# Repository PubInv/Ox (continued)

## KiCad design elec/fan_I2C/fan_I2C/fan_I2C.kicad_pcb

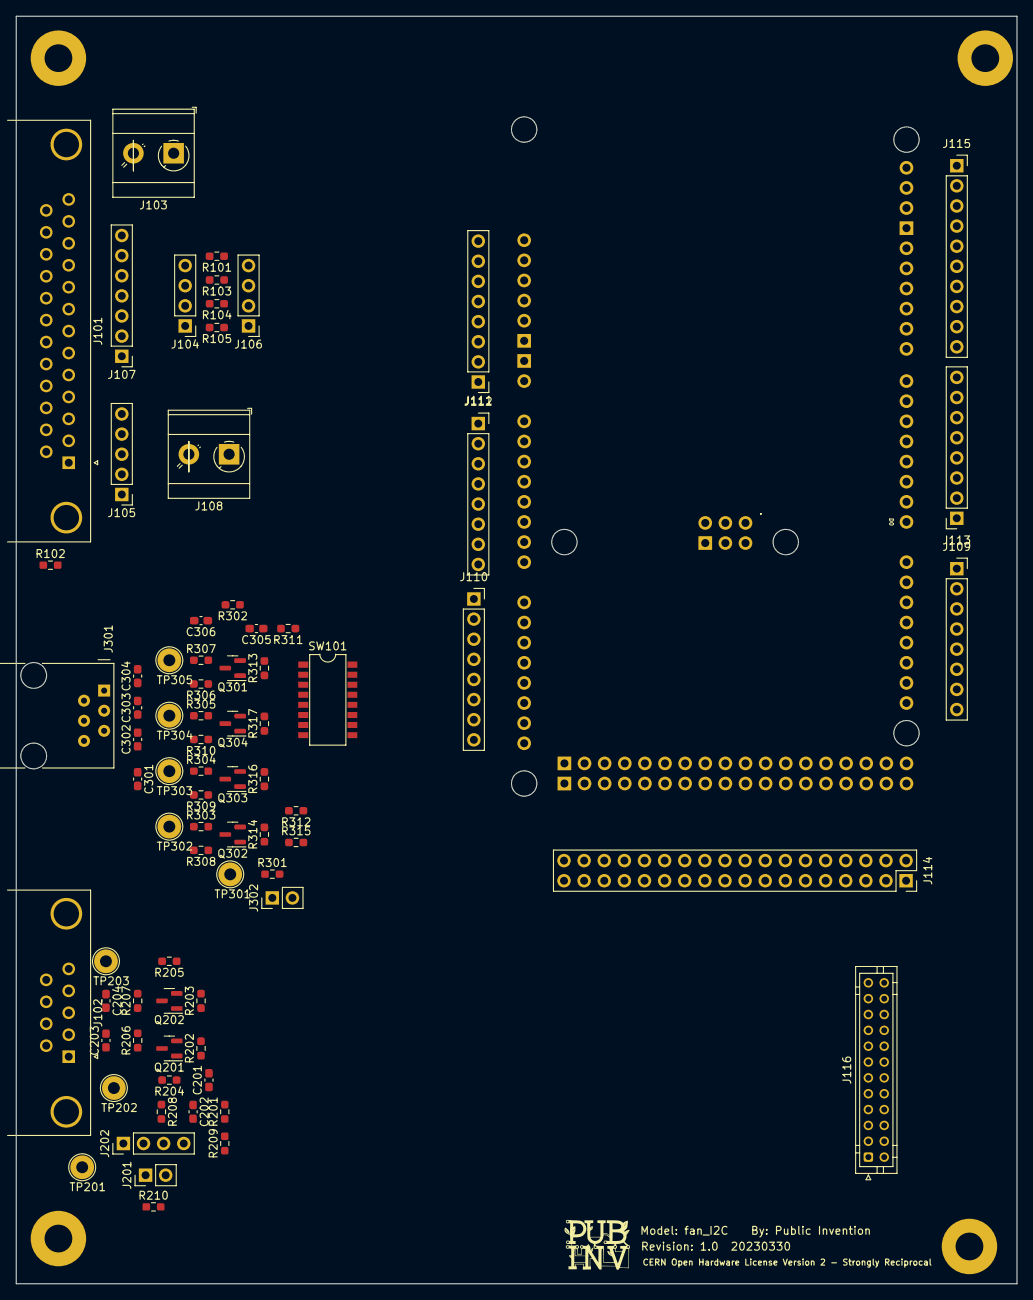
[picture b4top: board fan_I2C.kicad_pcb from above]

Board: 2 copper layers, 126.3 x 160.0 mm, 78 parts (0 on the bottom side), 123 nets, no tracks yet.

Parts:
C201, C202, C305, C306: 1uF; C_0603_1608Metric_Pad1.08x0.95mm_HandSolder
C203, C204, C301, C302, C303, C304: 39PF; C_0603_1608Metric_Pad1.08x0.95mm_HandSolder
J101: DB25_Female_MountingHoles; DSUB-25_Female_Horizontal_P2.77x2.84mm_EdgePinOffset4.94mm_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
J102: DB9_Female_MountingHoles; DSUB-9_Female_Horizontal_P2.77x2.84mm_EdgePinOffset4.94mm_H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
J103, J108: Screw_Terminal_01x02; TerminalBlock_MetzConnect_Type073_RT02602HBLU_1x02_P5.08mm_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
J104, J106, J202: Conn_01x04; PinHeader_1x04_P2.54mm_Vertical
J105: Conn_01x05; PinHeader_1x05_P2.54mm_Vertical
J107: Conn_01x07; PinHeader_1x07_P2.54mm_Vertical
J109, J110, J112, J113: Conn_01x08; PinSocket_1x08_P2.54mm_Vertical
J111: Conn_01x08; PinHeader_1x08_P2.54mm_Vertical
J114: Conn_02x18_Odd_Even; PinSocket_2x18_P2.54mm_Vertical
J115: Conn_01x10_MountingPin; PinSocket_1x10_P2.54mm_Vertical
J116: Conn_02x12_Odd_Even; JST_PHD_B24B-PHDSS_2x12_P2.00mm_Vertical
J201, J302: 0.100_2Pin; PinHeader_1x02_P2.54mm_Vertical
J301: RJ12_6P6C_HORZ; RJ12_Amphenol_54601
Q201, Q202, Q301, Q302, Q303, Q304: BSS138; SOT-23
R101, R103, R104, R105: 540R; R_0603_1608Metric_Pad0.98x0.95mm_HandSolder
R102, R209, R210, R303, R304, R305, R307, R312, R315: DNI; R_0603_1608Metric_Pad0.98x0.95mm_HandSolder
R201, R208, R301, R302, R311: 1R; R_0603_1608Metric_Pad0.98x0.95mm_HandSolder
R202, R203, R204, R205, R308, R313, R316, R317: 10K; R_0603_1608Metric_Pad0.98x0.95mm_HandSolder
R206, R207: 39R; R_0603_1608Metric_Pad0.98x0.95mm_HandSolder
R306, R309, R310, R314: 1K; R_0603_1608Metric_Pad0.98x0.95mm_HandSolder
SW101: SW_DIP_x08; SMDIP-16_L11.39_W6.7mm
TP201: I2C_VCC; TestPoint_Loop_D2.54mm_Drill1.5mm_Beaded
TP202: SCL_5V; TestPoint_Loop_D2.54mm_Drill1.5mm_Beaded
TP203: SDA_5V; TestPoint_Loop_D2.54mm_Drill1.5mm_Beaded
TP301: ControllerVCC; TestPoint_Loop_D2.54mm_Drill1.5mm_Beaded
TP302: CPIO; TestPoint_Loop_D2.54mm_Drill1.5mm_Beaded
TP303: SCK; TestPoint_Loop_D2.54mm_Drill1.5mm_Beaded
TP304: COPI; TestPoint_Loop_D2.54mm_Drill1.5mm_Beaded
TP305: nCS; TestPoint_Loop_D2.54mm_Drill1.5mm_Beaded
XA101: Arduino_Due_Shield

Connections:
5V3: J114.1, XA101.5V3 (5V)
5V4: J114.2, XA101.5V4 (5V)
+3.3V: J106.2, J111.5, R101.1, R103.1, R104.1, R105.1, R311.1, XA101.3V3 (3.3V)
+5V: J111.4, R302.1, XA101.5V1 (5V)
+12V: J302.2, R301.2
/I2C_LevelShift/+3V3Local: C201.1, Q201.1 (G), Q202.1 (G), R201.2, R202.1, R203.1
/I2C_LevelShift/+5LevelShift: R208.2, R209.2
/I2C_LevelShift/+5VLocal: C202.1, R204.1, R205.1, R208.1
/I2C_LevelShift/+12forSPIPeripherial: J201.2, R210.2
/I2C_LevelShift/I2C_VCC: J201.1, J202.1, R209.1, R210.1, TP201.1
/I2C_LevelShift/SCL_5V: C203.1, J102.2, J202.2, R206.1, TP202.1
/I2C_LevelShift/SDA_5V: C204.1, J102.4, J202.4, R207.1, TP203.1
/SPI_ControllerLevel_Shifter/+3V3Local: C305.1, Q301.1 (G), Q302.1 (G), Q303.1 (G), Q304.1 (G), R311.2, R313.1, R314.1, R316.1, R317.1
/SPI_ControllerLevel_Shifter/+5VLocal: C306.1, R302.2, R306.1, R308.1, R309.1, R310.1
/SPI_ControllerLevel_Shifter/CIPO: C301.1, J301.6, Q302.3 (D), R303.1, R308.2, TP302.1
/SPI_ControllerLevel_Shifter/COPI: C303.1, J301.2, Q304.3 (D), R305.1, R310.2, TP304.1
/SPI_ControllerLevel_Shifter/COPI_nCS: Q301.2 (S), R307.2, R313.2, SW101.1, SW101.2, SW101.3, SW101.4, SW101.5, SW101.6, SW101.7, SW101.8
/SPI_ControllerLevel_Shifter/C_SCK: C302.1, J301.4, Q303.3 (D), R304.1, R309.2, TP303.1
/SPI_ControllerLevel_Shifter/ControllerVcc: J301.5, J302.1, R301.1, TP301.1
/SPI_ControllerLevel_Shifter/nCS: C304.1, J301.1, Q301.3 (D), R306.2, R307.1, TP305.1
AREF: J115.3, XA101.AREF
CANR: J110.7, XA101.CANR (CANRX)
CANT: J110.8, XA101.CANT (CANTX)
CIPO: Q302.2 (S), R303.2, R312.2, R314.2, XA101.MISO (SPI_MISO)
COPI: Q304.2 (S), R305.2, R317.2, XA101.MOSI (SPI_MOSI)
D0: J113.1, XA101.D0 (D0/RX0)
D1: J113.2, XA101.D1 (D1/TX0)
D23: J109.7, J114.4, XA101.D23
D25: J114.6, XA101.D25
D27: J114.8, XA101.D27
D29: J114.10, XA101.D29
D31: J114.12, XA101.D31
D33: J114.14, XA101.D33
D35: J114.16, XA101.D35
D37: J114.18, XA101.D37
D39: J114.20, XA101.D39
D41: J114.22, XA101.D41
D43: J114.24, XA101.D43
D45: J114.26, XA101.D45
D47: J114.28, XA101.D47
D49: J114.30, XA101.D49
D51: J114.32, XA101.D51
DAC0: J110.5, XA101.DAC0
DAC1: J110.6, XA101.DAC1
GND: C201.2, C202.2, C203.2, C204.2, C301.2, C302.2, C303.2, C304.2, C305.2, C306.2, J101.0 (PAD), J102.0 (PAD), J102.3, J102.6, J102.7, J102.8, J102.9, J106.1, J108.1, J111.2, J111.3, J114.35, J114.36, J115.4, J202.3, J301.3, R102.2, R315.1, XA101.GND1 (GND), XA101.GND2 (GND), XA101.GND3 (GND), XA101.GND5 (GND), XA101.GND6 (GND)
unnamed: J101.1, J105.1
unnamed: J101.2, J105.2
unnamed: J101.3, J105.3
unnamed: J101.4, J105.4
unnamed: J101.5, J104.1, R105.2
unnamed: J101.6, J104.2, R104.2
unnamed: J101.7, J104.3, R103.2
unnamed: J101.8, J104.4, R101.2
unnamed: J101.9, J101.10, J101.11, J101.12, J103.2
unnamed: J101.13, J106.4
unnamed: J101.14, J101.15, J101.16, J101.17, J103.1, R102.1
unnamed: J101.18, J107.1
unnamed: J101.19, J107.2
unnamed: J101.20, J107.3
unnamed: J101.21, J107.4
unnamed: J101.22, J107.5
unnamed: J101.23, J107.6
unnamed: J101.24, J107.7
unnamed: J101.25, J106.3
unnamed: J105.5, J108.2
unnamed: J109.1, XA101.D14 (D14/TX3)
unnamed: J109.2, XA101.D15 (D15/RX3)
unnamed: J109.3, XA101.D16 (D16/TX2)
unnamed: J109.4, XA101.D17 (D17/RX2)
unnamed: J109.5, XA101.D18 (D18/TX1)
unnamed: J109.6, XA101.D19 (D19/RX1)
unnamed: J110.1, XA101.A8
unnamed: J110.2, XA101.A9
unnamed: J110.3, XA101.A10
unnamed: J110.4, XA101.A11
unnamed: J111.1, XA101.VIN
unnamed: J111.6, XA101.RST1 (RESET)
unnamed: J111.7, XA101.IORF (IOREF)
unnamed: J112.1, XA101.A0
unnamed: J112.2, XA101.A1
unnamed: J112.3, XA101.A2
unnamed: J112.4, XA101.A3
unnamed: J112.5, XA101.A4
unnamed: J112.6, XA101.A5
unnamed: J112.7, XA101.A6
unnamed: J112.8, XA101.A7
unnamed: J113.3, XA101.D2
unnamed: J113.4, XA101.D3
unnamed: J113.5, XA101.D4 (D4_CS1)
unnamed: J113.6, XA101.D5
unnamed: J113.7, XA101.D6
unnamed: J113.8, XA101.D7
unnamed: J114.3, XA101.D22
unnamed: J114.5, XA101.D24
unnamed: J114.7, XA101.D26
unnamed: J114.9, XA101.D28
unnamed: J114.11, XA101.D30
unnamed: J114.13, XA101.D32
unnamed: J114.15, XA101.D34
unnamed: J114.17, XA101.D36
unnamed: J114.19, XA101.D38
unnamed: J114.21, XA101.D40
unnamed: J114.23, XA101.D42
unnamed: J114.25, XA101.D44
unnamed: J114.27, XA101.D46
unnamed: J114.29, XA101.D48
unnamed: J114.31, XA101.D50
unnamed: J114.33, XA101.D52 (D52_CS2)
unnamed: J114.34, XA101.D53
unnamed: J115.5, XA101.D13
unnamed: J115.6, XA101.D12
unnamed: J115.7, XA101.D11
unnamed: J115.8, XA101.D10 (D10_CS0)
unnamed: J115.9, XA101.D9
unnamed: J115.10, XA101.D8
unnamed: Q201.3 (D), R204.2, R206.2
unnamed: Q202.3 (D), R205.2, R207.2
unnamed: R312.1, R315.2
SCL: Q201.2 (S), R202.2, XA101.D21 (D21/SCL)
SCL1: J115.1, XA101.SCL1
SDA: Q202.2 (S), R203.2, XA101.D20 (D20/SDA)
SDA1: J115.2, XA101.SDA1
SPI_SCK: Q303.2 (S), R304.2, R316.2, XA101.SCK (SPI_SCK)

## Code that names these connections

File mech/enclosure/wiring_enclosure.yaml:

#templates for generalized connectors
#utilizes https://github.com/wireviz/WireViz
templates:
  - &template_con
    type: Anderson Power SB50 SB
    subtype:  Dual
    pinlabels: [V+, V-, V+, V-]
  - &template_wire
    gauge: 6.00 mm2
    length: 0.2
    colors: [RD,BK,RD,BK]
    category: bundle
  - &ac_hookup
        wirecount: 3
        length: 0.2 //15ft
        category: bundle
        colors: [BK,WH,GN]
        gauge: 12 awg
  - &tc_hookup
        wirecount: 2
        length: 0.02
        category: bundle
        colrs: [YL,RD]
cables:   # dictionary of all used cables and wires
  W0:
    gauge: 1 mm2
    show_equiv: true
    length: 0.5
    color_code: IEC
    wirecount: 3
    category: bundle

  W1:    # unique cable designator/name
    gauge: 6.0 mm2
    # defaults to false; can auto-convert between mm2 and AWG and display the result when set to true
    show_equiv: true
     # <int/float> is assumed to be in meters unless <unit> is specified
                                # e.g. length: 2.5 -> assumed to be 2.5 m
                                # or   length: 2.5 ft -> "ft" is used as the unit
                                # Units are not converted during BOM generation;
                                # different units result in separate BOM entries.
    length: 0.5
    #color_code: IEC
    wirecount: 2
    category: bundle
    colors: [RD,BK]     # list of colors (see below)
    wirelabels: [V+,V-] # optional; one label for each wire
  W2:
    gauge: 0.25 mm2
    show_equiv: true
    length: 0.5
    color_code: IEC
    wirecount: 24
    category: bundle

  W3: #TC 1
    <<: *tc_hookup
    length: 0.2
    show_equiv: true
  W4: #TC 2
    <<: *tc_hookup
    length: 0.2
    show_equiv: true
  W5: #TC 3
    <<: *tc_hookup
    length: 0.2
    show_equiv: true
  W6: 
    <<: *template_wire

  W7: #DC powersupply_12v
    <<: *ac_hookup

  W8: #DC powersupply_24v
    <<: *ac_hookup

  W9: #DC powersupply_programmable
    <<: *ac_hookup

  power_cord:
      wirecount: 3
      length: 5000 //15ft
      category: bundle
      colors: [BK,WH,GN]

connectors:  # dictionary of all used connectors
  ferrule_spade:  # unique connector designator/name
    style: simple
    autogenerate: true
    type: Spade ferrule
    subtype: spade
  ferrule_crimp:
    style: simple
    autogenerate: true
    type: Crimp ferrule
    subtype: 0.25 mm²
    color: YE

  CN2:
    type: JST PHDR-24VS
    subtype: female
    pincount: 24
    pinlabels: [VS+, VO+, VS-, VO-, POK, GND, PAR, VSET, EN-, GND, EN+, AUX, ACI, GND, VCI, GND, AUX, GND, SCL, SDA, AUX, GND, RX, TX]

  X1:
    type: D-Sub
    subtype: male
    pincount: 9
#    pinlabels: []

  X2:
    type: D-Sub
    subtype: male
    pincount: 25
    pinlabels: [NP,NP,NP,NP,PWM1,PWM2,PWM3,PWM4,+12v,+12v,+12v,+12v,NP,GND,GND,GND,GND,PWM5,PWM6,PWM7,PWM8,PWM9,PWM10,PWM11,NP]
    notes: Pin 5-8 have 470 Ohm Pull Up resistors
  X3:
    <<: *template_con
  X4:
    <<: *template_con
  X5:
    <<: *template_con
  X6:
    <<: *template_con
  Arduino_Due:
    type: jumpers
    pinlabels: [TX,RX, TX1, RX1, SDA, SCL, VIN, GND, A0, A1, A2, A3, A4, A5, A6, A7, A8, A9, A10, A11, D0, D1, D2, D3, D4, D5, D6, D7, D8, D9, D10, D11, D12, D13, D14, D15, D16, D17, D18, D19, D20, D21, 3.3V, GND]
  Fan_Interface:
    type: jumpers
    pinlabels: [ nFAN1_PWM, FAN1_FG, nFAN2_PWM, FAN2_FG, FAN3_FG, nFAN3_PWM, FAN4_FG, nFAN4_PWM]

connections:  # list of all connections to be made between cables and connectors
  -
    - ferrule_crimp
    - W1: [1-2]
    - ferrule_crimp
  -
    - CN2: [1-24]
    - W2: [1-24]
    - ferrule_crimp
  -
    - X1: [5,2,3]
    - W0: [1-3]
    - Arduino_Due: [D0,D1,D21]
  -
    - X3: [1-4]
    - W3: [1-4]
    - ferrule_crimp
  -
    - X4: [1-4]
    - W4: [1-4]
    - ferrule_crimp
  -
    - X5: [1-4]
    - W5: [1-4]
    - ferrule_crimp
  -
     - ferrule_crimp
     - W7: [1-3]
  -  
     - ferrule_crimp
     - Arduino_Due: [A0, D4, D9, D18, D19, D51, 3.3V, GND]
     - nFAN1_PWM
     - FAN1_FG
     - nFAN2_PWM
     - FAN2_FG
     - FAN3_FG
     - nFAN3_PWM
     - FAN4_FG
     - nFAN4_PWM
     
#  -

#additional_bom_items:  # custom items to add to BOM
#  - zip ties           # BOM item (see below)

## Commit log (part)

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2023-08-17 Add U1 rack mount on right.
2023-08-17 Add a multitransform but it overwrites other features and DB9 has dependancy cycle and not recompute.
2023-08-17 Update README.md
    Add the OEDCS1-Aug-17.JPG image to the README.md at mech/enclosure/AssemblyPhotos
2023-08-17 imported Lee's changed inputs into the folder Control Board,
    Also added in Robert's pin labels
    ToDo: clean up broken links, and import in the layout files from Lee's project
    Clean up the fan control pinout, the DB25 is a bit of a mess
    consider using IDC to DB25 connectors for ease of assembly and installation.
2023-08-18 Add Lees PublicInvention submodule library. Update Control V1 project and schematic for new library.
2023-08-19 Rename Due CFC Pinouts to Due CFC Pinouts.md
2023-08-19 Update README.md
    Add wiring of thermocouple amplifiers of Unit 1.
2023-08-21 Update README.md
    Update fan supply voltage and indicated switched.
2023-08-21 Switch to FAN POWER.
2023-08-21 Update README.md
    Fix, swap, function on DB25 pins 3 and 7
2023-08-21 Add net names to fan controler block.
2023-08-22 Update README.md
    Add links for On line schematic viewing from **Kicanvas** of the current schematics.
2023-08-22 Add fan circuits. Add thermocouple interface circuits.
2023-08-23 fixing a bug in the data logging, seems to be working now
2023-08-23 Add footrpint to Max31850 module.
2023-08-24 debugged getting the fan test working again
2023-08-24 Add footprints for thermoucouple modules to schematic and PCB. This commit does NOT capture the library changes.
2023-08-24 Flip the front panel around.
2023-08-24 fan is now working properly
2023-08-24 Update schematic for MCP9600 I2C thermocouple.
2023-08-25 Next and place thermocouple boards.
2023-08-25 Fix swome ERC errors.
2023-08-25 Add header sockets. Refine PCB placement, temprature sensors.
2023-08-26 Update README.md
    Begin Due Pin Wiring Table
2023-08-27 very significant rewrite and simplication of the main algorithms
2023-08-27 Update README.md
    Add more details to Due wiring table. Up to D19.
2023-08-27 Net name congruancy to D35. Add named test points.
2023-08-27 Update README.md
    Finish the Due pin table.
2023-08-27 Update README.md
    Update of Due Pin Number table resolving some "???" and more.
2023-08-28 Update README.md
    Update to Due pin wiring after team review.
2023-08-28 Changes during team review.
2023-08-28 Lots of routing. Lots remaining.
2023-08-28 Finishe routing on enlarged perimeter.
2023-08-28 fixing bug #148 by inceasing MAX_TASKS and some other improvements
2023-08-28 using sentinel numbers in report
2023-08-29 Fixing bug #175
2023-08-30 Update parts in schematic for BOM generation.
2023-08-30 Add BOM spread sheet and a JLCPCB BOM.
2023-08-30 Update README.md
    Update the Control v1 README.md with KICanvas link to the PCB
2023-08-30 Add footprints to KiCad board. Make simple Due and Ethernte boards for pullin into FreeCAD assembly and do so.
2023-08-30 Preparation for the stage2 heater code
2023-08-30 changing obsolete file name
2023-08-30 further refactoring of state machine
2023-08-31 significant refactoring to make Stage2 heater
2023-08-31 stage2 report working now
2023-08-31 Update README.md
    Make more descriptive of the scope of the content.
2023-08-31 Add folder and a README.md for capture of Serial number 2 fabrication.
2023-08-31 Update README.md
    Add more information about serial number 2 build.
2023-08-31 some progress on Stage2 desgin
2023-09-01 debugging of stage2 related code
2023-09-02 working mostly on improving ability to survive resets and other debugging
2023-09-03 some more refacotrings (no build attempted yet
2023-09-03 now the heater code compiles
2023-09-04 checking if isinf on ohms values to avoid string being printed and messing up Cumulocity
2023-09-04 Update README.md
    Add the acronym OEDCS with the explanation.
2023-09-04 removing intermediate directories that we used for passing code but are now breaking the build on Windows machines (or maytbe all)
2023-09-05 Remove submodult to Watchdog example code.
2023-09-05 in middle of debuggin, stacks[0] point on COG_HAL appears to be incorrect by the time it used
2023-09-05 Update Stage2_Heater.md
    added ethernet shield pin references for SPI
2023-09-06 Add imaes of Controller V1 PCB and Assys from JLCPCB.
2023-09-06 Add a Controller support bracket.
2023-09-06 Update README.md
    With PWA
2023-09-06 fixed majore bug that was preventing the addition of the ramp up time
2023-09-06 Image Making print out more accurate.
2023-09-06 Create README.md
    Describe the files.
2023-09-07 turning off debugging statments
2023-09-07 Update Watchdog to rev 6. Save to flash only when D12 low. Increment flash count on reset. Add serial number to structure.
2023-09-08 Change PCB gap on ControllerSupport from 1mm to 2mm.
2023-09-09 Update README.md
    Spaces to format better.
2023-09-11 Create networking
2023-09-12 Changing from D4 to D5 for temperature reads
2023-09-12 Incrementing version for change in thermocouple pin.
2023-09-13 added stage2 hal changes
2023-09-13 adding target fore due_stage2_heater
2023-09-13 intermediate files, not compiling
2023-09-13 compiling, but untested
2023-09-13 committing some debugging statements
2023-09-13 Update Stage2_Heater.md
    updated pinout docs
2023-09-14 OnePinHeater refactoring, changes to makefile
2023-09-14 major refactoring of network code to remove it from tha task and put it in the hal
2023-09-14 Adding two files
2023-09-14 creatign Stage2 Network class
2023-09-14 refactoring file names
2023-09-14 Add files via upload
    Full resolution Serial number 2 photographs.
2023-09-15 fix networking code
2023-09-15 fix W5x00 init error message
2023-09-15 adding immature test program that does not seem to have any bad readings even with fan on
2023-09-15 revving version number
2023-09-16 beginning of the 5-knob work
2023-09-16 Update README.md
    Add more MAC addresses
2023-09-16 initial checkin, reading commands but commands do nothing, this branch is broken for now
2023-09-16 Some bugs from 263 fixed, but Network may not be working.
2023-09-16 some improvements
2023-09-17 intermediate waypoint
2023-09-17 Update state_machine_manager.cpp
    enabled ramp down target temp, otherwise computeRampDnTargetTemp returns float t unmodified
2023-09-17 signifianct work, and some realizations for simplifications
2023-09-18 fix memory leaks inside parsing state params and phases
2023-09-18 adding DueFlashStorage library
2023-09-18 adding wattage limitation
2023-09-18 Update README.md
    Link to an issue for how to find an ODECS IP address.
2023-09-18 Create README.md
    Description of Files / Folders
2023-09-18 latest
2023-09-19 removing param script retrieval
2023-09-19 providing a back door for testing when you don't have 3 thermocouples as a compile time switch
2023-09-19 change generation of max address to set last bit 0 for cfc and 1 for stage2
2023-09-19 revert my last change
2023-09-20 minor udp fix
2023-09-20 intermediate code, unknown state
2023-09-20 Update README.md
    Add MAC for OEDCS Serial number 2.
2023-09-20 moving back to 3.11.0 for Dallas OneWire
2023-09-20 reveting to use standard thermocooples for Stage2
2023-09-21 removing stray debugging statements
2023-09-21 fixing but with temperature jump
2023-09-22 fixing global start temperature bug
2023-09-22 Fixing an incorrect variable, passing GLOBAL_RECENT_TEMP when it should have been WARM_UP_BEGIN_TIME, cause ramp up to be too high
2023-09-22 update to debugging
2023-09-22 Add Due mechanical files. Add step for the Due Ethernet Control v1 assembly.
2023-09-22 compatability with SPI thermocouple boards and to ensure there is always an initial good read before compair
2023-09-23 Update Fan 4-wire cable interface
2023-09-26 Improving Make Target
2023-09-27 now compiles Stage2Heater code successfully
2023-09-27 changing precision of printed value
2023-09-27 Add simulation file and result as PNG.
2023-09-27 Update README.md
    Add a README.md to explain the simulation and simulation files.
2023-09-27 Update platformio.ini
    added support for rPi needs to have arm compiler defined
    per
    https://github.com/platformio/platform-ststm32/issues/404#issuecomment-673693211
2023-09-27 Update README.md
    Correct some novel spelling.
    Improve formatting of notes.
    Add description of limitation of the simulation.
2023-09-28 Add a simulation workbook to RCRC simulation.
2023-09-28 Update README.md
    Update with link to this schematic.
2023-09-28 changing PID Tunings
2023-10-02 Update polarity of connections to the GPOLY to correct the signs of the terms in the output.
2023-10-04 improve casting in TC toleration time math and fixing major bug in the use of the PID controller.
2023-10-05 adding debugging to the test program by using a fork with more
2023-10-06 Create README.md
    Add markdown with previews of photos.
2023-10-06 Update README.md
    Add link to folder of OEDCS Serial number 1 device photos.
2023-10-07 Update for JLCPCB part number of J10
2023-10-10 Copy PCB version 1.0 to version 1v1 and delete stale files. No other changes.
2023-10-10 Fix J10 backwards.
2023-10-11 Place many of new components. Still need to place SSR parts.
2023-10-11 Update README.md
    Update most of the PCB information. THIS PCB is not yet finished.
2023-10-11 Added schematic components for display header
2023-10-11 cosmetic schematic layouc changes
2023-10-11 Add power supply enable circuits. Add shutdown button.
2023-10-12 Make first cut JLCPCB BOM.
2023-10-12 unified 1R and 1R0 references
2023-10-12 Update README.md
    Add display_interface.kicad_sch to the README.MD
2023-10-12 Create Safety and Hazards Failure Effects Mode Analysis
2023-10-13 Some component placement for display and I2C.
2023-10-13 Still working on a few JLCPCB part numbers for components, headers - sockets.
2023-10-13 Fill ground.
2023-10-13 Getting close to order of PWAs for Control 1v1.
2023-10-13 Add the files JLCPCB modified for their order process.
2023-10-13 Add Breadboard30P.
2023-10-16 Add the Manufacturing files and notes as used for the JLCPCB order on 20231016,
2023-10-17 Holes in flanges but they disappear.
2023-10-17 Changes to change headders to sockets. Scockets for thermcouple amplifiers.
2023-10-17 updated manufacturing bom and positino files
2023-10-18 A 3D file for the Control V1 printed wiring assembly.
2023-10-18 Update README.md
    Update screen shot of 3D view of Control V1.1 PWA.
2023-10-18 Add holes to Front Panel, but not yet located fully.
2023-10-18 Add center holes to flanges and to Front Panel.
2023-10-18 Create README.md
    A read me for the 2U enclosure drawings.
2023-10-19 Add an IP64 M12 Bulkhead to wire for I2C pressue sensor.
2023-10-19 Add the TwoU_Assembly_TwinPower.FCStd drawing.
2023-10-19 Adding arduino test code for display and heater
2023-10-19 Add initial files for heartbeat task.
2023-10-19 Heartbeat task toggeling LED_BUILTIN
2023-10-19 Make a constant for the Heartbeat period.
2023-10-20 Increment version to Rev: 0.3.9, add new files for power_monitor_task. Compiles but does nothing.
2023-10-20 Power monitor task measuring SENSE_24V and reporing it as voltage and reporting power good or bad.
2023-10-21 Add TYSETC enclosure for BigTreeTech display and place on front panel of TwoU.
2023-10-23 Call a power monitor function in CogTask::_run(). Made duplicate function in cog_task.cpp.
2023-10-24 added new task to periodically log the state of the machine seperately from other tasks
2023-10-24 adding new function
2023-10-27 verified log recordings work
2023-10-27 Update debug.h
    fix hang when building on arm
2023-11-06 Rearrange heat source and RC elements for clarity.
2023-11-09 Create SBC setup instructions
2023-11-10 initial pcb design for high current, constant current psu
2023-11-13 added both proposed and development configuartion
2023-11-13 updated SBC setup instructions
2023-11-15 Added a set function to change period of a task
    Fixed a few bugs and typos
    Added logRecorderTask pointer to MachineState and added function calls to SetPeriod for
    Critical Fault and Emergency Shutdown to increase the periodicity of the reporting.
    possibly should add a dedicated function to call the logging function on state transitions.
